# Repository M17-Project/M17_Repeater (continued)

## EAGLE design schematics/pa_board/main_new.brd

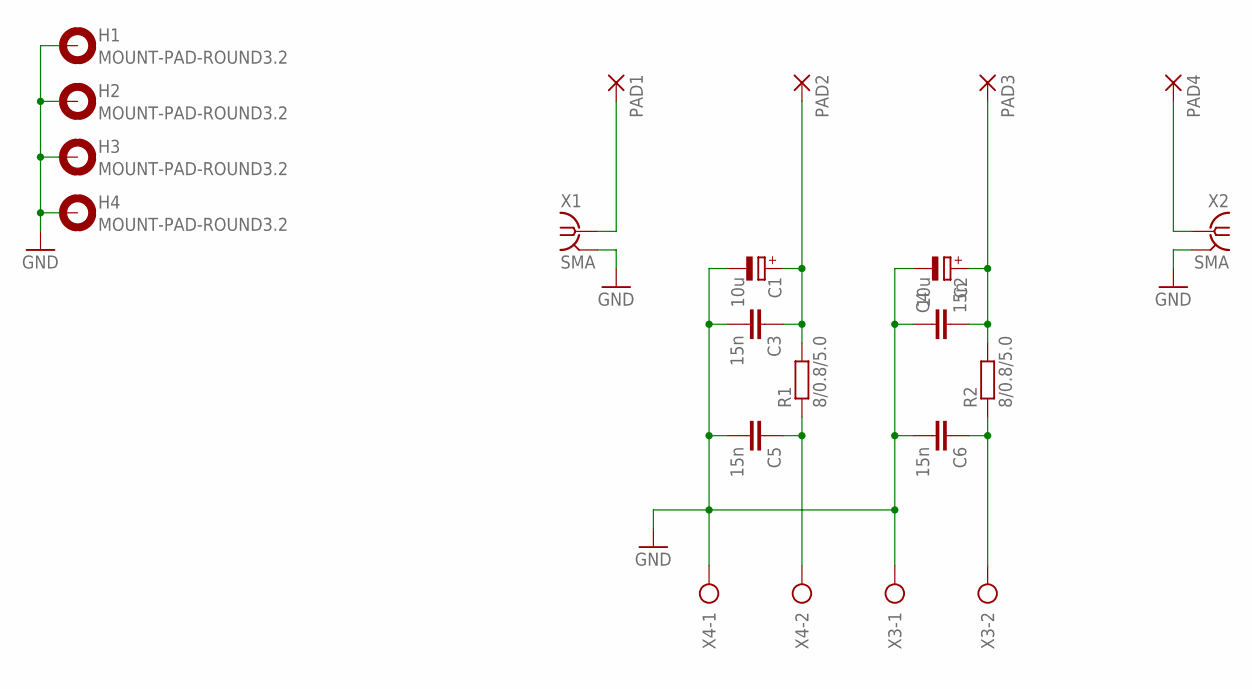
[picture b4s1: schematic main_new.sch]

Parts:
C1, C2: 10u; E5-8,5
C3, C4, C5, C6: 15n; C050-030X075
H1, H2, H3, H4: MOUNT-PAD-ROUND3.2; 3,2-PAD
PAD1, PAD2, PAD3, PAD4: SMD5; SMD2,54-5,08
R1, R2: 8/0.8/5.0; 0411/12
X1, X2: SMA; J502-ND-142-0711-821/826
X3, X4: AK500/2

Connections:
GND: C1.-, C2.-, C3.2, C4.1, C5.2, C6.2, H1.B3,2, H2.B3,2, H3.B3,2, H4.B3,2, X1.G@1 (2), X1.G@2 (2), X1.G@3 (2), X1.G@4 (2), X2.G@1 (2), X2.G@2 (2), X2.G@3 (2), X2.G@4 (2), X3.1, X4.1
unnamed: PAD1.1, X1.1
unnamed: PAD4.1, X2.1
unnamed: C6.1, R2.1, X3.2
unnamed: C2.+, C4.2, PAD3.1, R2.2
unnamed: C1.+, C3.1, PAD2.1, R1.2
unnamed: C5.1, R1.1, X4.2

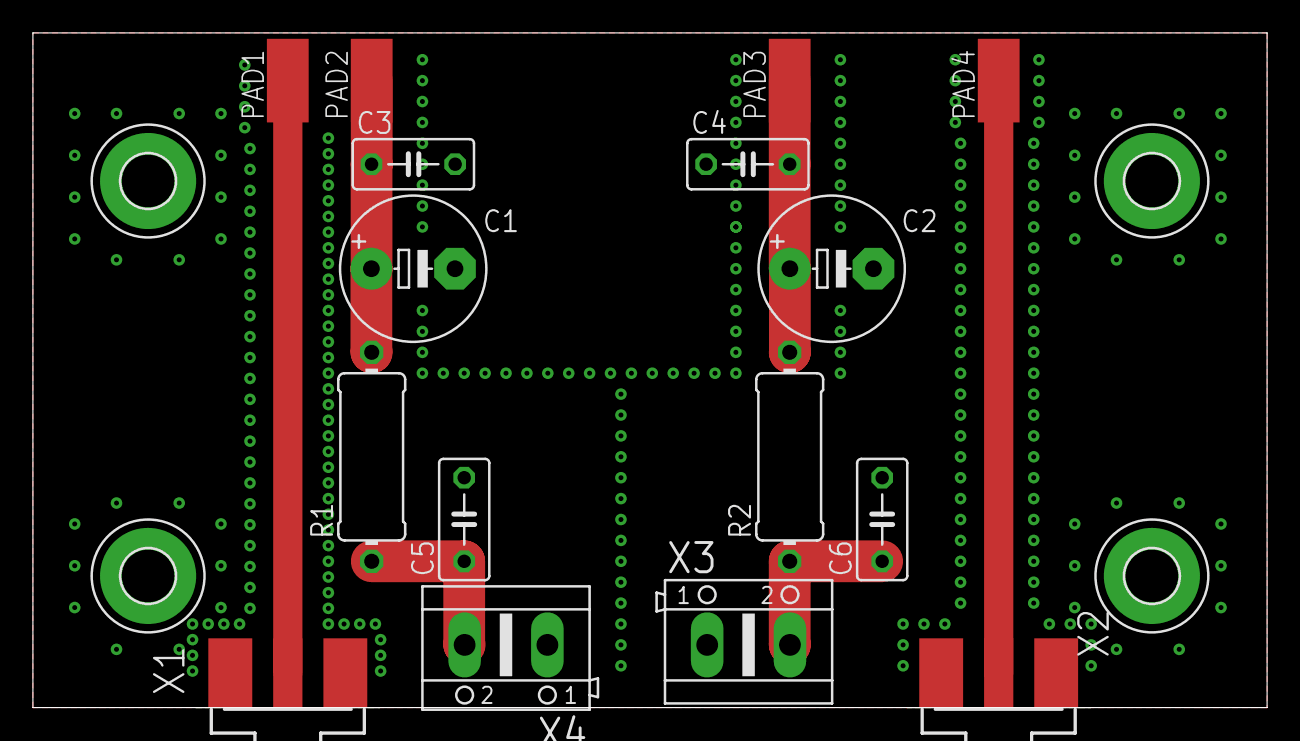
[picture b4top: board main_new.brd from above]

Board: 2 copper layers, 75.0 x 41.0 mm, 20 parts (0 on the bottom side), 7 nets.

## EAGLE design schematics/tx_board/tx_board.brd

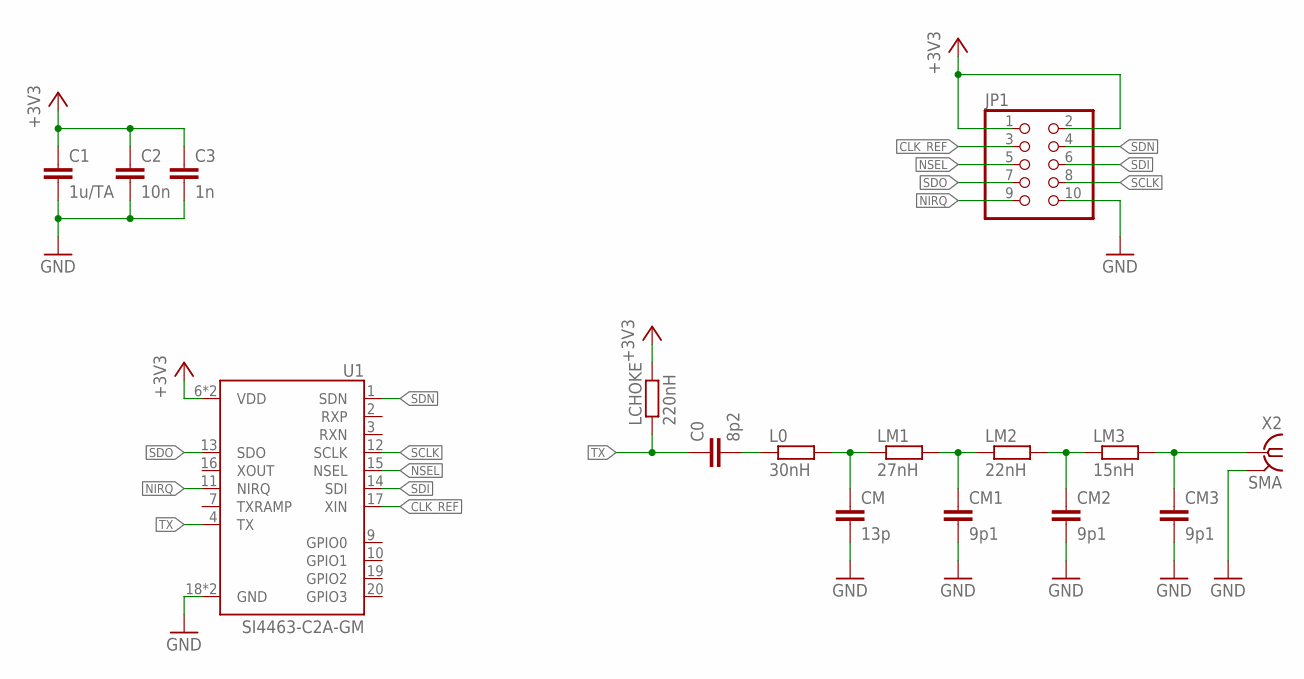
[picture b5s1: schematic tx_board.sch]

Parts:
C0: 8p2; C0805
C1: 1u/TA; C1206
C2: 10n; C0805
C3: 1n; C0805
CM: 13p; C0805
CM1, CM2, CM3: 9p1; C0805
JP1: PINHD-2X5/90; 2X05/90
L0: 30nH; R0805
LCHOKE: 220nH; R0805
LM1: 27nH; R0805
LM2: 22nH; R0805
LM3: 15nH; R0805
U1: SI4463-C2A-GM; QFN50P400X400X90-20N
X2: SMA; J502-ND-142-0701-871/876

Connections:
+3V3: C1.1, C2.1, C3.1, JP1.1, JP1.2, LCHOKE.2, U1.6 (VDD), U1.8 (VDD)
CLK_REF: JP1.3, U1.17 (XIN)
GND: C1.2, C2.2, C3.2, CM.2, CM1.2, CM2.2, CM3.2, JP1.10, U1.18 (GND), U1.21 (GND), X2.G@1 (2), X2.G@2 (2), X2.G@3 (2), X2.G@4 (2)
unnamed: CM2.1, LM2.2, LM3.1
unnamed: CM3.1, LM3.2, X2.1
unnamed: C0.2, L0.1
unnamed: CM.1, L0.2, LM1.1
unnamed: CM1.1, LM1.2, LM2.1
NIRQ: JP1.9, U1.11 (NIRQ)
NSEL: JP1.5, U1.15 (NSEL)
SCLK: JP1.8, U1.12 (SCLK)
SDI: JP1.6, U1.14 (SDI)
SDN: JP1.4, U1.1 (SDN)
SDO: JP1.7, U1.13 (SDO)
TX: C0.1, LCHOKE.1, U1.4 (TX)

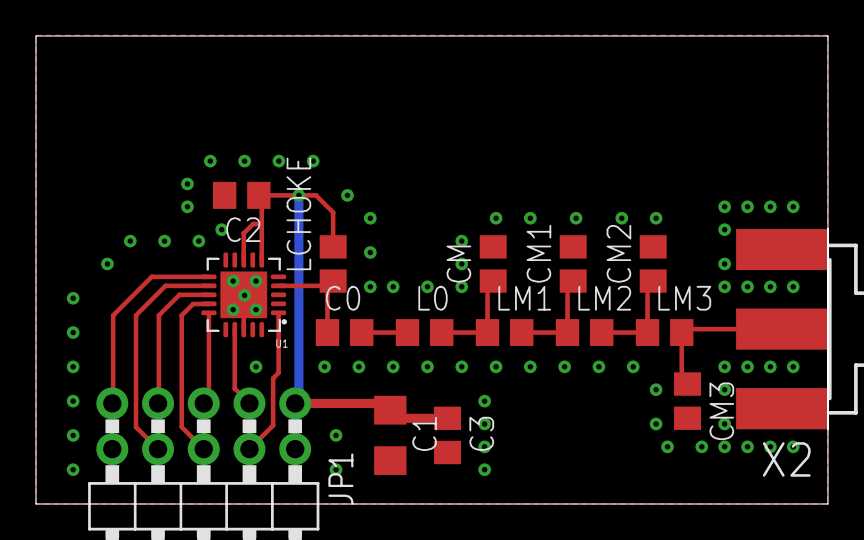
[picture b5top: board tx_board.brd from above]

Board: 2 copper layers, 44.0 x 26.0 mm, 16 parts (0 on the bottom side), 15 nets.

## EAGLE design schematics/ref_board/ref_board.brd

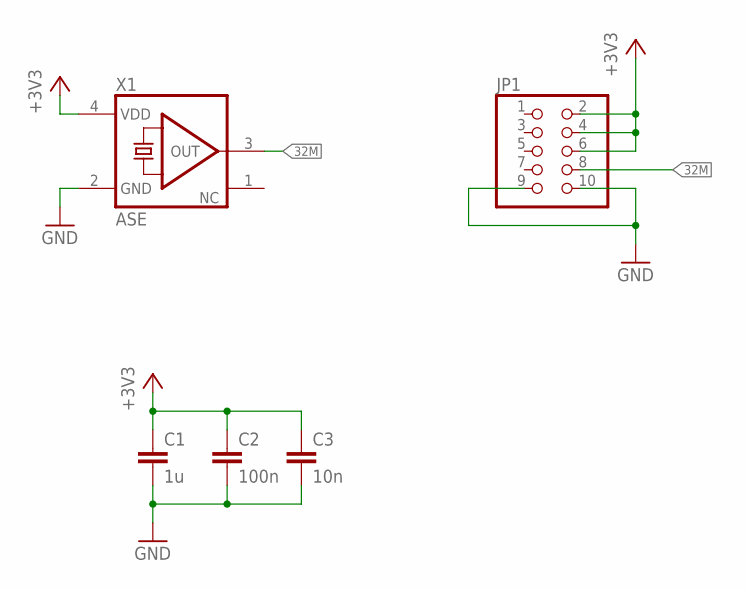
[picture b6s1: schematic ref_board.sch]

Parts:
C1: 1u; C1206
C2: 100n; C0805
C3: 10n; C0805
JP1: PINHD-2X5/90; 2X05/90
X1: ASE

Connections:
32M: JP1.8, X1.3 (OUT)
+3V3: C1.1, C2.1, C3.1, JP1.2, JP1.4, JP1.6, X1.4 (VDD)
GND: C1.2, C2.2, C3.2, JP1.9, JP1.10, X1.2 (GND)

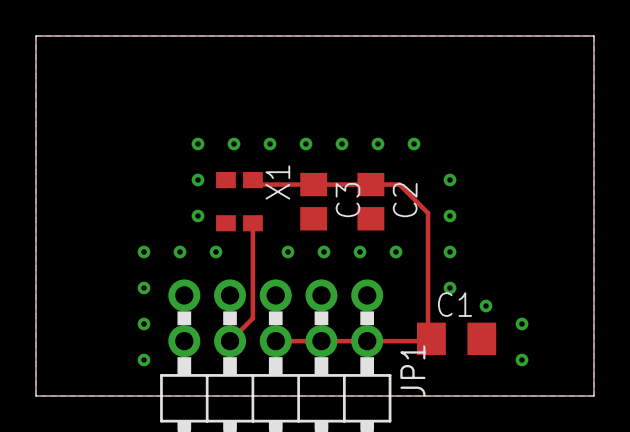
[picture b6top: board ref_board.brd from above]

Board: 2 copper layers, 31.0 x 20.0 mm, 5 parts (0 on the bottom side), 3 nets.

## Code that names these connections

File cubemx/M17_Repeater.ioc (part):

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Mcu.Name=STM32F777VITx
Mcu.Package=LQFP100
Mcu.UserName=STM32F777VITx
PA0/WKUP.Signal=ADCx_IN0
PA1.Signal=ADCx_IN1
PA10.Mode=Asynchronous
PA10.Signal=USART1_RX
PA13.Mode=Serial_Wire
PA13.Signal=SYS_JTMS-SWDIO
PA14.Mode=Serial_Wire
PA14.Signal=SYS_JTCK-SWCLK
PA15.GPIOParameters=GPIO_Label
PA15.GPIO_Label=LED_0
PA15.Signal=GPIO_Output
PA2.Signal=ADCx_IN2
PA3.Signal=ADCx_IN3
PA4.Signal=COMP_DAC1_group
PA5.GPIOParameters=GPIO_Label
PA5.GPIO_Label=RX_SCK
PA5.Mode=Full_Duplex_Master
PA5.Signal=SPI1_SCK
PA6.GPIOParameters=GPIO_Label
PA6.GPIO_Label=RX_MISO
PA6.Mode=Full_Duplex_Master
PA6.Signal=SPI1_MISO
PA7.GPIOParameters=GPIO_Label
PA7.GPIO_Label=RX_MOSI
PA7.Mode=Full_Duplex_Master
PA7.Signal=SPI1_MOSI
PA9.Mode=Asynchronous
PA9.Signal=USART1_TX
PB0.GPIOParameters=GPIO_Speed,PinState,GPIO_PuPd,GPIO_Label,GPIO_ModeDefaultOutputPP
PB0.GPIO_Label=RX_SDN
PB0.GPIO_ModeDefaultOutputPP=GPIO_MODE_OUTPUT_PP
PB0.GPIO_PuPd=GPIO_NOPULL
PB0.GPIO_Speed=GPIO_SPEED_FREQ_VERY_HIGH
PB0.PinState=GPIO_PIN_SET
PB0.Signal=GPIO_Output
PB1.GPIOParameters=GPIO_Speed,GPIO_PuPd,GPIO_Label,GPIO_ModeDefaultOutputPP
PB1.GPIO_Label=LCD_RS
PB1.GPIO_ModeDefaultOutputPP=GPIO_MODE_OUTPUT_PP
PB1.GPIO_PuPd=GPIO_NOPULL
PB1.GPIO_Speed=GPIO_SPEED_FREQ_VERY_HIGH
PB1.Signal=GPIO_Output
PB10.GPIOParameters=GPIO_Speed,GPIO_PuPd,GPIO_Label,GPIO_ModeDefaultOutputPP
PB10.GPIO_Label=LCD_RES
PB10.GPIO_ModeDefaultOutputPP=GPIO_MODE_OUTPUT_PP
PB10.GPIO_PuPd=GPIO_NOPULL
PB10.GPIO_Speed=GPIO_SPEED_FREQ_VERY_HIGH
PB10.Signal=GPIO_Output
PB12.GPIOParameters=GPIO_Speed,PinState,GPIO_PuPd,GPIO_Label,GPIO_ModeDefaultOutputPP
PB12.GPIO_Label=TX_SDN
PB12.GPIO_ModeDefaultOutputPP=GPIO_MODE_OUTPUT_PP
PB12.GPIO_PuPd=GPIO_NOPULL
PB12.GPIO_Speed=GPIO_SPEED_FREQ_VERY_HIGH
PB12.PinState=GPIO_PIN_SET
PB12.Signal=GPIO_Output
PB13.GPIOParameters=GPIO_Label
PB13.GPIO_Label=TX_SCK
PB13.Mode=Full_Duplex_Master
PB13.Signal=SPI2_SCK
PB14.GPIOParameters=GPIO_Label
PB14.GPIO_Label=TX_MISO
PB14.Mode=Full_Duplex_Master
PB14.Signal=SPI2_MISO
PB15.GPIOParameters=GPIO_Label
PB15.GPIO_Label=TX_MOSI
PB15.Mode=Full_Duplex_Master
PB15.Signal=SPI2_MOSI
PB2.GPIOParameters=GPIO_Speed,GPIO_PuPd,GPIO_Label,GPIO_ModeDefaultOutputPP
PB2.GPIO_Label=LCD_RW
PB2.GPIO_ModeDefaultOutputPP=GPIO_MODE_OUTPUT_PP
PB2.GPIO_PuPd=GPIO_NOPULL
PB2.GPIO_Speed=GPIO_SPEED_FREQ_VERY_HIGH
PB2.Signal=GPIO_Output
PB4.GPIOParameters=GPIO_Label
PB4.GPIO_Label=ENC_B
PB4.Signal=S_TIM3_CH1
PB5.GPIOParameters=GPIO_Label
PB5.GPIO_Label=ENC_A
PB5.Signal=S_TIM3_CH2
PC0.GPIOParameters=GPIO_Speed,GPIO_Label
PC0.GPIO_Label=LCD_CS1
PC0.GPIO_Speed=GPIO_SPEED_FREQ_VERY_HIGH
PC0.Signal=GPIO_Output
PC1.GPIOParameters=GPIO_Speed,GPIO_Label
PC1.GPIO_Label=LCD_CS2
PC1.GPIO_Speed=GPIO_SPEED_FREQ_VERY_HIGH
PC1.Signal=GPIO_Output
PC10.GPIOParameters=GPIO_Label
PC10.GPIO_Label=LED_1
PC10.Signal=GPIO_Output
PC11.GPIOParameters=GPIO_Label
PC11.GPIO_Label=LED_2
PC11.Signal=GPIO_Output
PC12.GPIOParameters=GPIO_Label
PC12.GPIO_Label=LED_3
PC12.Signal=GPIO_Output
PC2.GPIOParameters=GPIO_Speed,GPIO_Label
PC2.GPIO_Label=LCD_CS3
PC2.GPIO_Speed=GPIO_SPEED_FREQ_VERY_HIGH
PC2.Signal=GPIO_Output
PC4.GPIOParameters=GPIO_Speed,PinState,GPIO_Label
PC4.GPIO_Label=RX_CS
PC4.GPIO_Speed=GPIO_SPEED_FREQ_VERY_HIGH
PC4.PinState=GPIO_PIN_SET
PC4.Signal=GPIO_Output
PC5.GPIOParameters=GPIO_Label,GPIO_ModeDefaultEXTI
PC5.GPIO_Label=RX_NIRQ
PC5.GPIO_ModeDefaultEXTI=GPIO_MODE_IT_FALLING
PC5.Signal=GPXTI5
PD0.GPIOParameters=GPIO_Label
PD0.GPIO_Label=LED_4
PD0.Signal=GPIO_Output
PD1.GPIOParameters=GPIO_Label
PD1.GPIO_Label=LED_5
PD1.Signal=GPIO_Output
PD12.GPIOParameters=GPIO_Speed,GPIO_Label
PD12.GPIO_Label=LCD_PWM
PD12.GPIO_Speed=GPIO_SPEED_FREQ_HIGH
PD12.Signal=S_TIM4_CH1
PD13.GPIOParameters=GPIO_ModeDefaultPP,GPIO_Speed,GPIO_PuPd,GPIO_Label
PD13.GPIO_Label=PWM_FAN_L
PD13.GPIO_ModeDefaultPP=GPIO_MODE_AF_PP
PD13.GPIO_PuPd=GPIO_NOPULL
PD13.GPIO_Speed=GPIO_SPEED_FREQ_HIGH
PD13.Signal=S_TIM4_CH2
PD14.GPIOParameters=GPIO_ModeDefaultPP,GPIO_Speed,GPIO_PuPd,GPIO_Label
PD14.GPIO_Label=PWM_FAN_R
PD14.GPIO_ModeDefaultPP=GPIO_MODE_AF_PP
PD14.GPIO_PuPd=GPIO_NOPULL
PD14.GPIO_Speed=GPIO_SPEED_FREQ_HIGH
PD14.Signal=S_TIM4_CH3
PD2.GPIOParameters=GPIO_PuPd,GPIO_Label,GPIO_ModeDefaultEXTI
PD2.GPIO_Label=BTN_3
PD2.GPIO_ModeDefaultEXTI=GPIO_MODE_IT_FALLING
PD2.GPIO_PuPd=GPIO_NOPULL
PD2.Signal=GPXTI2
PD3.GPIOParameters=GPIO_PuPd,GPIO_Label,GPIO_ModeDefaultEXTI
PD3.GPIO_Label=BTN_2
PD3.GPIO_ModeDefaultEXTI=GPIO_MODE_IT_FALLING
PD3.GPIO_PuPd=GPIO_NOPULL
PD3.Signal=GPXTI3
PD4.GPIOParameters=GPIO_PuPd,GPIO_Label,GPIO_ModeDefaultEXTI
PD4.GPIO_Label=BTN_1
PD4.GPIO_ModeDefaultEXTI=GPIO_MODE_IT_FALLING
PD4.GPIO_PuPd=GPIO_NOPULL
PD4.Signal=GPXTI4
PD7.GPIOParameters=GPIO_PuPd,GPIO_Label,GPIO_ModeDefaultEXTI
PD7.GPIO_Label=BTN_0
PD7.GPIO_ModeDefaultEXTI=GPIO_MODE_IT_FALLING
PD7.GPIO_PuPd=GPIO_NOPULL
PD7.Signal=GPXTI7
PD8.GPIOParameters=GPIO_Speed,PinState,GPIO_Label
PD8.GPIO_Label=TX_CS
PD8.GPIO_Speed=GPIO_SPEED_FREQ_VERY_HIGH
PD8.PinState=GPIO_PIN_SET
PD8.Signal=GPIO_Output
PD9.GPIOParameters=GPIO_Label,GPIO_ModeDefaultEXTI
PD9.GPIO_Label=TX_NIRQ
PD9.GPIO_ModeDefaultEXTI=GPIO_MODE_IT_FALLING
PD9.Signal=GPXTI9
PE0.GPIOParameters=GPIO_Label,GPIO_ModeDefaultEXTI
PE0.GPIO_Label=PTT
PE0.GPIO_ModeDefaultEXTI=GPIO_MODE_IT_FALLING
PE0.Signal=GPXTI0
PE1.GPIOParameters=GPIO_Label,GPIO_ModeDefaultEXTI
PE1.GPIO_Label=ENC_BTN
PE1.GPIO_ModeDefaultEXTI=GPIO_MODE_IT_FALLING
PE1.Signal=GPXTI1
PE10.GPIOParameters=GPIO_Speed,PinState,GPIO_PuPd,GPIO_Label,GPIO_ModeDefaultOutputPP
PE10.GPIO_Label=LCD_DB2
PE10.GPIO_ModeDefaultOutputPP=GPIO_MODE_OUTPUT_PP
PE10.GPIO_PuPd=GPIO_NOPULL
PE10.GPIO_Speed=GPIO_SPEED_FREQ_VERY_HIGH
PE10.PinState=GPIO_PIN_RESET
PE10.Signal=GPIO_Output
PE11.GPIOParameters=GPIO_Speed,PinState,GPIO_PuPd,GPIO_Label,GPIO_ModeDefaultOutputPP
PE11.GPIO_Label=LCD_DB3
PE11.GPIO_ModeDefaultOutputPP=GPIO_MODE_OUTPUT_PP
PE11.GPIO_PuPd=GPIO_NOPULL
PE11.GPIO_Speed=GPIO_SPEED_FREQ_VERY_HIGH
PE11.PinState=GPIO_PIN_RESET
PE11.Signal=GPIO_Output
PE12.GPIOParameters=GPIO_Speed,PinState,GPIO_PuPd,GPIO_Label,GPIO_ModeDefaultOutputPP
PE12.GPIO_Label=LCD_DB4
PE12.GPIO_ModeDefaultOutputPP=GPIO_MODE_OUTPUT_PP
PE12.GPIO_PuPd=GPIO_NOPULL
PE12.GPIO_Speed=GPIO_SPEED_FREQ_VERY_HIGH
PE12.PinState=GPIO_PIN_RESET
PE12.Signal=GPIO_Output
PE13.GPIOParameters=GPIO_Speed,PinState,GPIO_PuPd,GPIO_Label,GPIO_ModeDefaultOutputPP
PE13.GPIO_Label=LCD_DB5
PE13.GPIO_ModeDefaultOutputPP=GPIO_MODE_OUTPUT_PP
PE13.GPIO_PuPd=GPIO_NOPULL
PE13.GPIO_Speed=GPIO_SPEED_FREQ_VERY_HIGH
PE13.PinState=GPIO_PIN_RESET
PE13.Signal=GPIO_Output
PE14.GPIOParameters=GPIO_Speed,PinState,GPIO_PuPd,GPIO_Label,GPIO_ModeDefaultOutputPP
PE14.GPIO_Label=LCD_DB6
PE14.GPIO_ModeDefaultOutputPP=GPIO_MODE_OUTPUT_PP
PE14.GPIO_PuPd=GPIO_NOPULL
PE14.GPIO_Speed=GPIO_SPEED_FREQ_VERY_HIGH
PE14.PinState=GPIO_PIN_RESET
PE14.Signal=GPIO_Output
PE15.GPIOParameters=GPIO_Speed,PinState,GPIO_PuPd,GPIO_Label,GPIO_ModeDefaultOutputPP
PE15.GPIO_Label=LCD_DB7
PE15.GPIO_ModeDefaultOutputPP=GPIO_MODE_OUTPUT_PP
PE15.GPIO_PuPd=GPIO_NOPULL
PE15.GPIO_Speed=GPIO_SPEED_FREQ_VERY_HIGH
PE15.PinState=GPIO_PIN_RESET
PE15.Signal=GPIO_Output
PE2.GPIOParameters=GPIO_Label
PE2.GPIO_Label=TP7
PE2.Signal=GPIO_Output
PE3.GPIOParameters=GPIO_Label
PE3.GPIO_Label=TP8
PE3.Signal=GPIO_Output
PE6.GPIOParameters=GPIO_Label,GPIO_ModeDefaultEXTI
PE6.GPIO_Label=TAMPER
PE6.GPIO_ModeDefaultEXTI=GPIO_MODE_IT_RISING_FALLING
PE6.Signal=GPXTI6
PE7.GPIOParameters=GPIO_Speed,PinState,GPIO_PuPd,GPIO_Label,GPIO_ModeDefaultOutputPP
PE7.GPIO_Label=LCD_E
PE7.GPIO_ModeDefaultOutputPP=GPIO_MODE_OUTPUT_PP
PE7.GPIO_PuPd=GPIO_NOPULL
PE7.GPIO_Speed=GPIO_SPEED_FREQ_VERY_HIGH
PE7.PinState=GPIO_PIN_RESET
PE7.Signal=GPIO_Output
PE8.GPIOParameters=GPIO_Speed,PinState,GPIO_PuPd,GPIO_Label,GPIO_ModeDefaultOutputPP
PE8.GPIO_Label=LCD_DB0
PE8.GPIO_ModeDefaultOutputPP=GPIO_MODE_OUTPUT_PP
PE8.GPIO_PuPd=GPIO_NOPULL
PE8.GPIO_Speed=GPIO_SPEED_FREQ_VERY_HIGH
PE8.PinState=GPIO_PIN_RESET
PE8.Signal=GPIO_Output
PE9.GPIOParameters=GPIO_Speed,PinState,GPIO_PuPd,GPIO_Label,GPIO_ModeDefaultOutputPP
PE9.GPIO_Label=LCD_DB1
PE9.GPIO_ModeDefaultOutputPP=GPIO_MODE_OUTPUT_PP
PE9.GPIO_PuPd=GPIO_NOPULL
PE9.GPIO_Speed=GPIO_SPEED_FREQ_VERY_HIGH
PE9.PinState=GPIO_PIN_RESET
PE9.Signal=GPIO_Output
PH0/OSC_IN.Mode=HSE-External-Clock-Source
PH0/OSC_IN.Signal=RCC_OSC_IN
PH1/OSC_OUT.Mode=HSE-External-Clock-Source
PH1/OSC_OUT.Signal=RCC_OSC_OUT
RCC.HSE_VALUE=16000000
RCC.SYSCLKFreq_VALUE=216000000
RCC.SYSCLKSource=RCC_SYSCLKSOURCE_PLLCLK
board=custom

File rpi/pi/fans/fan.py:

import RPi.GPIO as GPIO
import time

from w1thermsensor import W1ThermSensor
from smbus2 import SMBus
from mcp3208 import MCP3208

#Consts
T_SENSOR_1="000009a5e43c"
T_SENSOR_2="000009a60a09"
PCF_CTRL = 0x21
PCF_DATA = 0x20

#CTRL
OE_1  = 0
OE_2  = 1
OE_3  = 2
CLK_EN= 3
CLR   = 4
LATCH = 5
FAN_R = 6
FAN_L = 7

#vars
fan_L_sp=20
fan_R_sp=20

#----------------------------------------------------------------------------
def GetRPM(fan):
	if fan == 0:
		val=(1<<OE_1)|(1<<OE_2)|(1<<OE_3)|(1<<CLR)|(1<<CLK_EN)
		i2c.write_byte(PCF_CTRL, val)
		time.sleep(0.001)
		val=(1<<OE_1)|(1<<OE_2)|(1<<OE_3)|(0<<CLR)|(1<<CLK_EN)
		i2c.write_byte(PCF_CTRL, val)
		time.sleep(0.001)
		val=(1<<OE_1)|(1<<OE_2)|(1<<OE_3)|(1<<CLR)|(1<<CLK_EN)
		i2c.write_byte(PCF_CTRL, val)
		time.sleep(0.001)
		val=(1<<OE_1)|(1<<OE_2)|(1<<OE_3)|(1<<CLR)|(0<<CLK_EN)|(1<<FAN_L)
		i2c.write_byte(PCF_CTRL, val)
		
		time.sleep(1)
		
		val=(1<<OE_1)|(1<<OE_2)|(1<<OE_3)|(1<<CLR)|(1<<CLK_EN)|(0<<FAN_L)
		i2c.write_byte(PCF_CTRL, val)
		time.sleep(0.001)
		val=(1<<OE_1)|(1<<OE_2)|(1<<OE_3)|(1<<CLR)|(1<<CLK_EN)|(1<<LATCH)
		i2c.write_byte(PCF_CTRL, val)
		time.sleep(0.001)
		val=(1<<OE_1)|(1<<OE_2)|(1<<OE_3)|(1<<CLR)|(1<<CLK_EN)|(0<<LATCH)
		i2c.write_byte(PCF_CTRL, val)
		
		time.sleep(0.001)
		val=(0<<OE_1)|(1<<OE_2)|(1<<OE_3)|(1<<CLR)|(1<<CLK_EN)
		i2c.write_byte(PCF_CTRL, val)
		time.sleep(0.001)
		r_1=i2c.read_byte(PCF_DATA)
		time.sleep(0.001)
		val=(1<<OE_1)|(1<<OE_2)|(1<<OE_3)|(1<<CLR)|(1<<CLK_EN)
		i2c.write_byte(PCF_CTRL, val)
		time.sleep(0.001)
		
		val=(1<<OE_1)|(0<<OE_2)|(1<<OE_3)|(1<<CLR)|(1<<CLK_EN)
		i2c.write_byte(PCF_CTRL, val)
		time.sleep(0.001)
		r_2=i2c.read_byte(PCF_DATA)
		time.sleep(0.001)
		val=(1<<OE_1)|(1<<OE_2)|(1<<OE_3)|(1<<CLR)|(1<<CLK_EN)
		i2c.write_byte(PCF_CTRL, val)
		time.sleep(0.001)
		
		val=(1<<OE_1)|(1<<OE_2)|(0<<OE_3)|(1<<CLR)|(1<<CLK_EN)
		i2c.write_byte(PCF_CTRL, val)
		time.sleep(0.001)
		r_3=i2c.read_byte(PCF_DATA)
		time.sleep(0.001)
		val=(1<<OE_1)|(1<<OE_2)|(1<<OE_3)|(1<<CLR)|(1<<CLK_EN)
		i2c.write_byte(PCF_CTRL, val)
		time.sleep(0.001)
	else:
		val=(1<<OE_1)|(1<<OE_2)|(1<<OE_3)|(1<<CLR)|(1<<CLK_EN)
		i2c.write_byte(PCF_CTRL, val)
		time.sleep(0.001)
		val=(1<<OE_1)|(1<<OE_2)|(1<<OE_3)|(0<<CLR)|(1<<CLK_EN)
		i2c.write_byte(PCF_CTRL, val)
		time.sleep(0.001)
		val=(1<<OE_1)|(1<<OE_2)|(1<<OE_3)|(1<<CLR)|(1<<CLK_EN)
		i2c.write_byte(PCF_CTRL, val)
		time.sleep(0.001)
		val=(1<<OE_1)|(1<<OE_2)|(1<<OE_3)|(1<<CLR)|(0<<CLK_EN)|(1<<FAN_R)
		i2c.write_byte(PCF_CTRL, val)
		
		time.sleep(1)
		
		val=(1<<OE_1)|(1<<OE_2)|(1<<OE_3)|(1<<CLR)|(1<<CLK_EN)|(0<<FAN_R)
		i2c.write_byte(PCF_CTRL, val)
		time.sleep(0.001)
		val=(1<<OE_1)|(1<<OE_2)|(1<<OE_3)|(1<<CLR)|(1<<CLK_EN)|(1<<LATCH)
		i2c.write_byte(PCF_CTRL, val)
		time.sleep(0.001)
		val=(1<<OE_1)|(1<<OE_2)|(1<<OE_3)|(1<<CLR)|(1<<CLK_EN)|(0<<LATCH)
		i2c.write_byte(PCF_CTRL, val)
		
		time.sleep(0.001)
		val=(0<<OE_1)|(1<<OE_2)|(1<<OE_3)|(1<<CLR)|(1<<CLK_EN)
		i2c.write_byte(PCF_CTRL, val)
		time.sleep(0.001)
		r_1=i2c.read_byte(PCF_DATA)
		time.sleep(0.001)
		val=(1<<OE_1)|(1<<OE_2)|(1<<OE_3)|(1<<CLR)|(1<<CLK_EN)
		i2c.write_byte(PCF_CTRL, val)
		time.sleep(0.001)
		
		val=(1<<OE_1)|(0<<OE_2)|(1<<OE_3)|(1<<CLR)|(1<<CLK_EN)
		i2c.write_byte(PCF_CTRL, val)
		time.sleep(0.001)
		r_2=i2c.read_byte(PCF_DATA)
		time.sleep(0.001)
		val=(1<<OE_1)|(1<<OE_2)|(1<<OE_3)|(1<<CLR)|(1<<CLK_EN)
		i2c.write_byte(PCF_CTRL, val)
		time.sleep(0.001)
		
		val=(1<<OE_1)|(1<<OE_2)|(0<<OE_3)|(1<<CLR)|(1<<CLK_EN)
		i2c.write_byte(PCF_CTRL, val)
		time.sleep(0.001)
		r_3=i2c.read_byte(PCF_DATA)
		time.sleep(0.001)
		val=(1<<OE_1)|(1<<OE_2)|(1<<OE_3)|(1<<CLR)|(1<<CLK_EN)
		i2c.write_byte(PCF_CTRL, val)
		time.sleep(0.001)
		
	return (r_1|(r_2<<8)|(r_3<<16))*15

#----------------------------------------------------------------------------
i2c = SMBus(1)
adc = MCP3208()

GPIO.setmode(GPIO.BCM)
GPIO.setwarnings(False)
GPIO.setup(12, GPIO.OUT)
GPIO.setup(18, GPIO.OUT)
 
fan_L = GPIO.PWM(12, 500)
fan_R = GPIO.PWM(18, 500)
fan_L.start(fan_L_sp)
fan_R.start(fan_R_sp)

val=(1<<OE_1)|(1<<OE_2)|(1<<OE_3)|(0<<CLR)|(1<<CLK_EN)
i2c.write_byte(PCF_CTRL, val)
val=(1<<OE_1)|(1<<OE_2)|(1<<OE_3)|(1<<CLR)|(1<<CLK_EN)
i2c.write_byte(PCF_CTRL, val)

while True:
	sensor = W1ThermSensor(W1ThermSensor.THERM_SENSOR_DS18B20, T_SENSOR_1)
	temp_1 = sensor.get_temperature()
	sensor = W1ThermSensor(W1ThermSensor.THERM_SENSOR_DS18B20, T_SENSOR_2)
	temp_2 = sensor.get_temperature()

	left_fan=GetRPM(0)
	right_fan=GetRPM(1)
	
	u_psu=0
	u_bat=0
	i_bat=0
	
	for i in range(1000):
		u_psu+=adc.read(0)
		u_bat+=adc.read(1)
		i_bat+=adc.read(2)-adc.read(3)
		
	u_psu/=1000.0
	u_bat/=1000.0
	i_bat/=1000.0
	u_psu*=14.46/1576.5
	u_bat*=14.51/1576.5*12.67/12.57 #might need to change coeffs
	i_bat/=100.0
	i_bat*=63.0/50.0;
	
	#overwrite
	with open('/var/www/html/vals.txt', 'r') as file:
		data = file.readlines()
		data[0] = str(temp_1) + '\n'
		data[1] = str(temp_2) + '\n'
		data[2] = str(fan_L_sp) + '\n'
		data[3] = str(fan_R_sp) + '\n'
		data[4] = str(u_bat) + '\n'
		data[5] = str(u_psu) + '\n'		
		data[6] = str(left_fan) + '\n'
		data[7] = str(right_fan) + '\n'
		data[8] = str(i_bat) + '\n'

		with open('/var/www/html/vals.txt', 'w') as file:
			file.writelines(data)

	#print("L=%dRPM, R=%dRPM" % (GetRPM(0), GetRPM(1)))

	#fan_L.ChangeDutyCycle(75)
	#fan_R.ChangeDutyCycle(75)

	#print("T_1=%.2f T_2=%.2f" % (temp_1, temp_2))
	
	#time.sleep(1)
